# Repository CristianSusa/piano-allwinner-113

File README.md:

# Piano with Dev Board LCPI-PC-T113
This piano is a college project for Embedded Systems and Electronic Systems Design. It uses the LCPI-PC-T113 development board with the Allwinner T113s chip running embedded Debian. The project includes the design of the PCB as well as the design of the enclosure. Notes on the development process are also included.

## Contents
Within this repository, you will find two folders:
* embedded-systems-development
* electronic-system-design

These folders serve as a step-by-step guide on how to construct the piano. They include files, construction notes, and suggestions for improvements in future versions.

Enjoy :D

# The Project

This piano is designed to provide a low-cost solution for portable musical instruments.

It has two main functions:

1. **Piano Mode** – When a key is pressed, the corresponding note is played through the speaker, just as you would expect from a traditional piano.

2. **Tutor Mode** – In this mode, a few preset songs are available. You can select one, and LEDs will light up to indicate which key to press next, guiding you through the melody step by step.

The piano is intended not only to function as a musical instrument, but also to serve as a learning tool for beginners.

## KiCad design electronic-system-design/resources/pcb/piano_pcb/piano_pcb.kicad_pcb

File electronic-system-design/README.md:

# Electronic Design
This section provides a detailed explanation of the project's electronic design, including key decisions, objectives, and development rationale. It aims to offer a broader perspective on the piano as a finished product, beyond just its functionality.

## The Piano
This project is a university-level design that combines embedded systems and electronic hardware development. It is built around the LCPI-PC-T113 development board, featuring the Allwinner T113s chip running embedded Debian.

The piano integrates both custom PCB and enclosure design, with additional documentation on the development process.

Its goal is to offer a low-cost, portable musical instrument that serves both as a basic piano and as an educational tool. It features two main modes:

- **Piano Mode** – Pressing a key plays the corresponding note through a speaker.
- **Tutor Mode** – LEDs guide the user through preloaded melodies, indicating which key to press next.

The system is designed for beginners, blending play and learning in a compact, accessible format.

## Inspiration
This piano is physically inspired by commercial MIDI controllers such as the **MiniLab 3** by Arturia, the **Akai MPK Mini**, and the **OP-1** by Teenage Engineering.

The goal is to build a portable device that gives users easy access to a piano wherever they are.

## Objectives
The goal of this project is to create an affordable, efficient, and scalable digital keyboard that works as a standalone device. It features an intuitive user interface.

### Main Objective
Design and build an affordable, energy-efficient, and user-friendly digital keyboard with an intuitive interface, capable of functioning independently and suitable for educational or experimental use.

### Specific Objectives
- **Ensure accessibility and affordability** by keeping the total cost of components below $300,000 COP, making the device viable for students and academic institutions.
- **Promote usability and learning** by including exercises or songs, reinforcing its role as a musical tutor and learning tool.
- **Guarantee energy efficiency and portability** by ensuring the device operates with a current draw of less than 1.5 A, allowing it to be powered by a standard 5V / 2A USB adapter or computer.

## Block Diagram

The proposed system configuration uses the LCPI-PC-T113 development board, featuring the Allwinner T113-S3 chip, as the main controller. A custom daughterboard (the PCB designed in this course) interfaces with it to connect the piano peripherals.

This separation of boards allows modularity: the main board can be reused in future projects, while the daughterboard is application-specific.

The system consists of five main modules:

- **Piano Inputs** – Controls 25 keys (from C4 to C6, covering 2 octaves) arranged in a 5×5 matrix. A *74HC595* shift register activates the columns, while a *74HC165* shift register reads the row states.
  - Shift registers reduce the number of required GPIOs and allow scalable input/output control.
  - ✅ *Pro*: Efficient use of GPIOs with minimal pin usage.
  - ❌ *Con*: Adds a small delay due to serial communication and requires precise clocking.

- **User Interface** – Includes an OLED display and three menu buttons.
  - A minimal interface was chosen to ensure simplicity and ease of navigation for all users.
  - ✅ *Pro*: Clear feedback and interaction with minimal components.
  - ❌ *Con*: Limited interactivity and no text input options.

- **Piano Outputs** – Manages 25 LEDs (one per key) using two *74HC595* shift registers in a 5×5 matrix. Audio output is routed from the board’s headphone jack to an 8-ohm speaker.
  - Using a matrix configuration minimizes wiring and enables efficient LED control in tutor mode.
  - ✅ *Pro*: Clear visual guidance during learning.
  - ❌ *Con*: Cannot light multiple arbitrary combinations without flickering unless advanced multiplexing is implemented.

- **Power** – Powered via a USB-C port providing 5V @ 2A, allowing compatibility with standard smartphone chargers.
  - USB-C is a modern standard and widely available.
  - ✅ *Pro*: Universal and accessible power source.
  - ❌ *Con*: Some connectors have mechanical instability depending on the cable used.

- **Serial Communication and Data** – Includes SD card storage and USB to TTL serial communication used during development and booting.
  - External storage and serial communication simplify testing and firmware updates.
  - ✅ *Pro*: Easy debugging and access to external data.
  - ❌ *Con*: Required workaround (jumpers) due to missing TX/RX pins in the schematic.

## Electrical Schematic

A total of 19 pins are used to connect the processor to the piano's peripherals. The image below shows the pinout configuration:

This layout was chosen to optimize routing and prioritize low-latency signals, like the key matrix and OLED interface.

The following sections explain how each module works and how the components are connected. All images are taken from the project schematic file `piano_pcb.kicad_sch`, available at `./resources/pcb/piano_pcb`.

### Keys Matrix
A 5×5 matrix is used to detect key presses, allowing us to read 25 distinct notes. A *74HC595* shift register sequentially activates each column, and a *74HC165* reads the row values. The switches are configured with pull-down resistors: a pressed key outputs logic `1`, and an unpressed key outputs `0`.

- ✅ *Pro*: Scalable and compact solution for multiple key inputs.
- ❌ *Con*: Requires careful debouncing and timing control in software.

### LEDs Matrix
Another 5×5 matrix is used to control the LEDs, which are mainly used in tutor mode to highlight the next key to press. Two *74HC595* shift registers manage the LED activation. LEDs use a pull-down configuration: a LED lights up when its cathode is at logic `1` and its anode is at logic `0`.

Coupling capacitors were used in the four integrated circuits to ensure proper power connection.

- ✅ *Pro*: Clean and organized visual feedback system.
- ❌ *Con*: Without current control, simultaneous activation of many LEDs can overload the system.

### I2C Screen
Initially, a 240×240 SPI screen was proposed for the menu interface. However, due to technical issues and budget/time constraints, we opted for a 128×64 I2C OLED display using the SSD1306 controller.

- ✅ *Pro*: Easy to integrate, widely supported, and consumes less power.
- ❌ *Con*: Lower resolution limits UI complexity.

### Menu Buttons
Three buttons (`Left`, `Enter`, and `Right`) allow the user to navigate the interface. All buttons use a pull-down configuration: pressing a button results in logic `1`, and releasing it results in logic `0`.

- ✅ *Pro*: Simple and intuitive user interaction.
- ❌ *Con*: Limited to basic menu navigation without multi-directional input.

Once the device is powered on and the application starts, the main menu is displayed with two options:

1. **Piano Mode** – Basic mode in which pressing a key plays the corresponding sound.
2. **Tutor Mode** – Guides the user through one of four built-in songs: `Estrellita`, `Cumpleaños Feliz`, `Los Pollitos`, and `Piratas del Caribe`.

### Power Input
Power is supplied through a USB-C female connector, chosen for its compatibility with most modern chargers. However, this decision turned out to be suboptimal — in practice, the connection can be unstable depending on the cable or connector, causing accidental shutdowns with slight movement.

To protect the circuit, an SS14 diode prevents reverse current and voltage spikes. Two 5.1kΩ resistors to ground ensure the USB-C port is used strictly for power and limits voltage to 5V.

- ✅ *Pro*: Broad compatibility and compact form factor.
- ❌ *Con*: Susceptible to disconnection if cable or socket is loose.

### Dev Board Integration
A custom symbol and footprint were created in KiCad to represent the LCPI-PC-T113 board and ensure proper alignment of connections.

The schematic shows the necessary connections for:
- **Shift register control** – `SER`, `CLK`, `LATCH`
- **Menu buttons** – input GPIOs for `Left`, `Enter`, and `Right`
- **OLED display** – `SDA`, `SCL` for I2C communication

- ✅ *Pro*: Accurate mapping of dev board pins in PCB layout.
- ❌ *Con*: Omission of serial TX/RX was a critical error, requiring manual correction with jumpers.

The serial communication was originally assigned to pins `PE2` and `PE3`, as shown in the pinout image above. However, these connections were not included in the schematic — a design oversight. As a workaround, jumpers were added in the physical prototype. This is one of the areas identified for improvement in future revisions.

## Materials
The piano consists of low-cost electronic components, including standard switches, LEDs, and diodes. The two most expensive parts of the build are the LCPI-PC-T113 development board and the custom-designed daughterboard (PCB). These will be detailed further in the cost breakdown.

Below is a list of the main components used:

- 25 × Tactile switches (1 per key)
- 25 × Red LEDs (1 per key for tutor feedback)
- 25 × 220 Ω resistors (for LED current limiting)
- 50 × 1N4148 diodes (for matrix input protection)
- 8 × 10 kΩ resistors (for pull-down configurations)
- 3 × 4-leg tactile menu switches (Left, Enter, Right)
- 4 × 8×2 pin sockets (for shift register and board connections)
- 3 × 74HC595 shift registers (2 for LED matrix, 1 for key matrix column activation)
- 1 × 74HC165 shift register (for key matrix row reading)
- 4 × 100 nF ceramic capacitors (for decoupling)
- 1 × SS14 Schottky diode (for reverse polarity protection)
- 2 × 5.1 kΩ resistors (for USB-C power configuration)
- 1 × USB-C female port (for 5V power input)
- 2 × Female header grids (to interface with dev board)

All components were selected for availability, cost-efficiency, and compatibility with hand soldering and prototyping.

## PCB Design

KiCad and LayoutEditor were the main tools used to design the PCB. The complete KiCad project is available at `./resources/pcb/piano_pcb`.

Returning to our five main modules, this section covers the design process for each one.

---

### Piano Inputs

The key matrix relies on mechanical keyboard switches and diodes. [This video](https://www.youtube.com/watch?v=8WXpGTIbxlQ) provided valuable guidance on mechanical keyboard design and was used as a reference. Its symbol and footprint library was also integrated and is available in `./resources/pcb/piano_pcb/Resources`.

Each note has a dedicated LED, so the layout prioritizes compactness while replicating a traditional piano key arrangement. Diodes are placed to the left of each key to prevent ghosting, and LEDs are positioned above or below the switch based on the note's vertical position.

Footprint used for the key switches:

### Piano Outputs

The LEDs are a core feature for the tutor mode. Each LED has a dedicated 220 Ω current-limiting resistor and a 1N4148 diode to avoid unwanted activation due to matrix effects (ghosting).

### User Interface

The menu buttons and display are located on the top edge of the piano for visibility and accessibility. The OLED screen symbol and footprint were manually created based on an initial SPI version, though later adapted to a 128×64 I2C display (SSD1306). The chosen I2C pins remained the same for mechanical compatibility.

### Power Input

This section presented the most soldering challenges due to two surface-mount components: the USB-C female connector and the SS14 Schottky diode. These were the only compatible models available in the local market and required careful placement.

### Devboard Interface

A custom footprint was created to place female headers in a "shield-like" fashion, aligning with the LCPI-PC-T113 board’s pinout. This allows reliable and modular interfacing between the devboard and the daughterboard.

---

### Construction

The PCB routing was done using the `FreeRouting` tool. All traces were set to 0.5 mm width, which is sufficient given the low current requirements of each signal. Both top and bottom layers were used, with several vias placed throughout the board—particularly around the key and LED matrices—due to the high density of connections.

The PCB was manufactured by **JLCPCB**, and the production files are available at `./resources/pcb/piano_pcb/production`.

Below are some images of the PCB layout and the assembled board:

Final soldered board:

## Case Design

The case was designed using **Adobe Illustrator**, vectorizing the pieces for laser cutting. The main PCB measures **314 mm × 150.5 mm**, and additional clearance was considered for the height of the devboard underneath (~15 mm), as well as the switches and screen above (~17.5 mm).

The design consists of two main parts:

1. **The Case** – Made of MDF and laser cut to encase the piano. It protects the electronics and gives structural support.

2. **The Keycaps** – A piece of laser-cut acrylic simulates the shape of piano keys. The transparency allows LED light to shine through during tutor mode, guiding the user visually.

The Adobe Illustrator and PDF files used in the process are available at `./resources/case/files`.

### Case Construction

Once all pieces were laser cut, assembly was done manually. The result is a lightweight, solid enclosure with custom-fit keycaps:

## User Menu

As mentioned earlier, three buttons (`Left`, `Enter`, and `Right`) are used to navigate the user interface. All buttons follow a pull-down configuration: pressing a button sends logic `1`, and releasing it returns to logic `0`.

Upon powering on the device and loading the main application, the user is presented with the main menu featuring two options:

1. **Piano Mode** – A classic mode where each key press immediately plays a corresponding note.
2. **Tutor Mode** – A guided mode where the user can select one of four built-in songs: `Estrellita`, `Cumpleaños Feliz`, `Los Pollitos`, and `Piratas del Caribe`.

Below is a simplified flow diagram of the navigation logic:

Some photos of the interface in action:

## Prototype
The final piano is a mix of effort, enthusiasms, challenges, copper, mdf, acrilic, electrons and music. Here are some photos.

## Technical Decisions Justification

### Choice of Main Microcontroller or IC
The project uses the **LCPI-PC-T113** development board based on the **Allwinner T113-S3** processor. This chip was selected because it can run a full embedded Debian OS, providing enough processing power to handle multiple peripherals (display, inputs, outputs, audio) while offering flexibility for expansion. Its ability to support real-time applications (like those built with Faust) made it an ideal platform for this kind of project.

### Technology Type: THT, SMD, or Mixed
A **mixed technology approach** was used. Most components (resistors, diodes, capacitors, shift registers, buttons, LEDs) are **THT (Through-Hole Technology)**, selected for ease of manual soldering and local availability. However, some components such as the **USB-C connector** and the **SS14 diode** are **SMD (Surface-Mount Device)** because they were only available in that format.

This hybrid approach balanced manufacturability, cost, and the team's ability to assemble the board by hand.

### Number of Layers
The PCB was designed with **two layers (top and bottom)**. This was necessary to route the large number of signals—especially in the key and LED matrices—without increasing manufacturing costs. Vias were used to interconnect the layers where needed, allowing for a more compact and efficient layout.

### Power and EMI Considerations
Power is supplied through a **USB-C female connector**, delivering 5 V at 2 A. A **Schottky SS14 diode** was added to protect the circuit from reverse current or voltage spikes. Two **5.1 kΩ pull-down resistors** ensure the port is used for power only. The overall current draw of the system is low, so thermal or EMI (electromagnetic interference) concerns were minimal. However, filtering and shielding could be added in future revisions if needed.

### Standards Applied
While no formal certification standard was strictly followed, the design referenced general best practices from the **IPC-2221** standard, including trace width, clearance, and via placement. These practices helped ensure a manufacturable PCB and reliable electrical performance during testing.

---

## Possible Improvements

- **Redesign the pinout** to include the `TX` and `RX` serial communication lines. These were missing in the original schematic and had to be patched with jumpers on the prototype.
- **Replace or reposition the USB-C connector** to improve physical connection stability. In its current location, small movements can interrupt power and shut down the piano.
- **Use dedicated LED drivers**, such as the TLC5940, to enable PWM per channel, reduce sound delay, and allow multiple notes to play simultaneously (polyphony).
- **Reintroduce the SPI screen** if software support issues are resolved, to take advantage of its higher resolution for better UI design.
- **Optimize power consumption** by adding sleep modes or auto-shutdown after inactivity.
- **Add EMI protection and filtering** for use in more demanding environments or for future compliance with electronic certification.
- **Follow full IPC standards** (such as IPC-2222 for general-purpose PCBs) to improve reliability, documentation quality, and potential for scaling production.

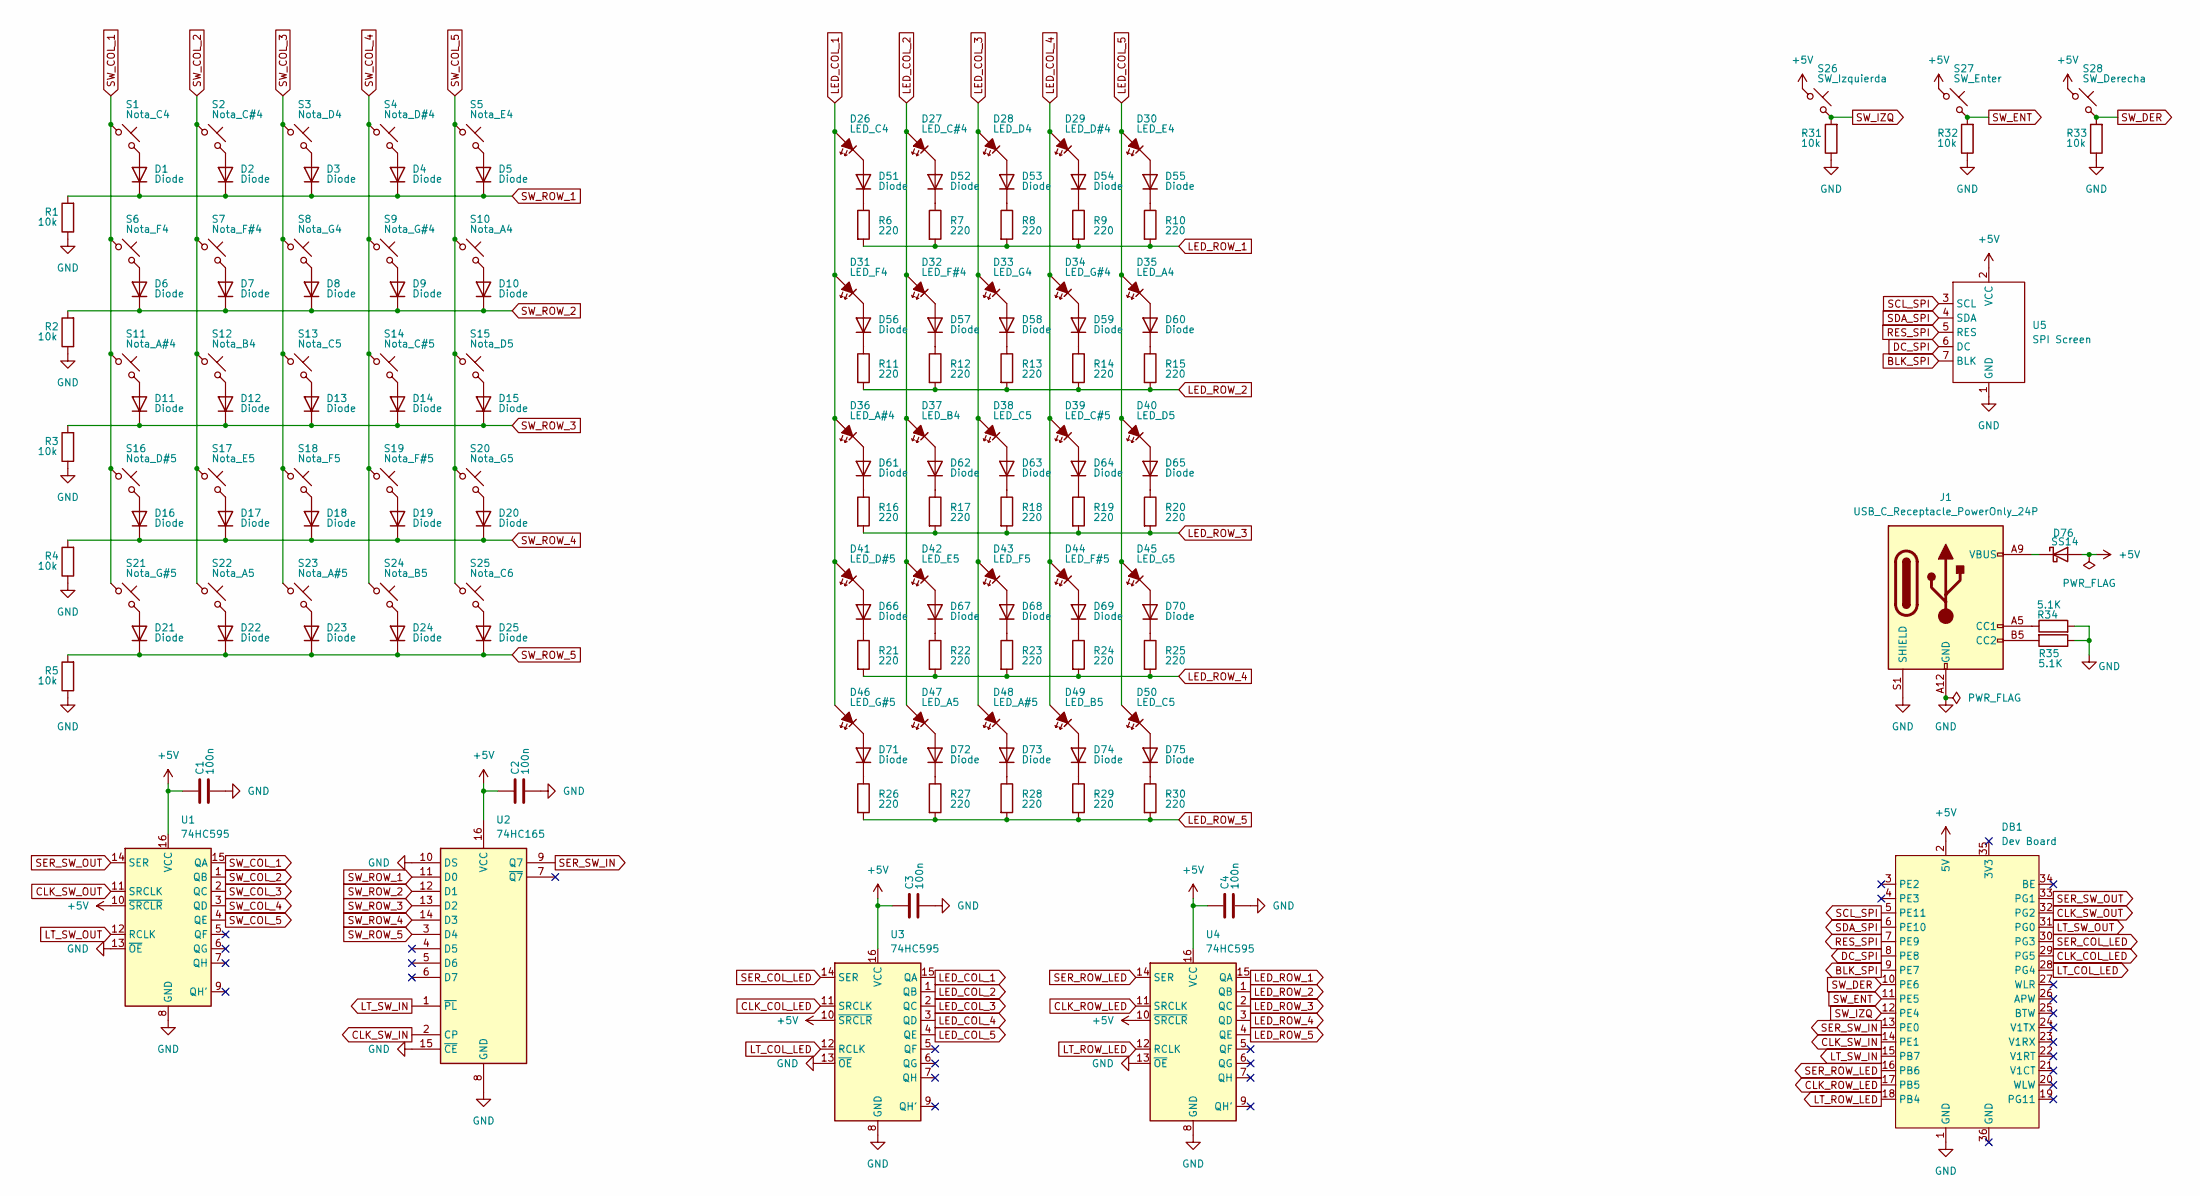
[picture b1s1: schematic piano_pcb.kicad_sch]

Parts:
C1, C2, C3, C4: 100n; CP_Radial_D8.0mm_P3.50mm
D1, D2, D3, D4, D5, D6, D7, D8, D9, D10, D11, D12, D13, D14, D15, D16, D17, D18, D19, D20, D21, D22, D23, D24, D25, D51, D52, D53, D54, D55, D56, D57, D58, D59, D60, D61, D62, D63, D64, D65, D66, D67, D68, D69, D70, D71, D72, D73, D74, D75: Diode; Diode_DO-35
D26: LED_C4; LED_D3.0mm
D27: LED_C#4; LED_D3.0mm
D28: LED_D4; LED_D3.0mm
D29: LED_D#4; LED_D3.0mm
D30: LED_E4; LED_D3.0mm
D31: LED_F4; LED_D3.0mm
D32: LED_F#4; LED_D3.0mm
D33: LED_G4; LED_D3.0mm
D34: LED_G#4; LED_D3.0mm
D35: LED_A4; LED_D3.0mm
D36: LED_A#4; LED_D3.0mm
D37: LED_B4; LED_D3.0mm
D38, D50: LED_C5; LED_D3.0mm
D39: LED_C#5; LED_D3.0mm
D40: LED_D5; LED_D3.0mm
D41: LED_D#5; LED_D3.0mm
D42: LED_E5; LED_D3.0mm
D43: LED_F5; LED_D3.0mm
D44: LED_F#5; LED_D3.0mm
D45: LED_G5; LED_D3.0mm
D46: LED_G#5; LED_D3.0mm
D47: LED_A5; LED_D3.0mm
D48: LED_A#5; LED_D3.0mm
D49: LED_B5; LED_D3.0mm
D76: SS14; D_SMA
DB1: Dev Board; Dev_Board_T113
J1: USB_C_Receptacle_PowerOnly_24P; USB_C_Receptacle_HRO_TYPE-C-31-M-17
R1, R2, R3, R4, R5, R31, R32, R33: 10k; R_Axial_DIN0204_L3.6mm_D1.6mm_P7.62mm_Horizontal
R6, R7, R8, R9, R10, R11, R12, R13, R14, R15, R16, R17, R18, R19, R20, R21, R22, R23, R24, R25, R26, R27, R28, R29, R30: 220; R_Axial_DIN0204_L3.6mm_D1.6mm_P7.62mm_Horizontal
R34, R35: 5.1K; R_Axial_DIN0204_L3.6mm_D1.6mm_P7.62mm_Horizontal
S1: Nota_C4; MX_PCB_1.00u
S2: Nota_C#4; MX_PCB_1.00u
S3: Nota_D4; MX_PCB_1.00u
S4: Nota_D#4; MX_PCB_1.00u
S5: Nota_E4; MX_PCB_1.00u
S6: Nota_F4; MX_PCB_1.00u
S7: Nota_F#4; MX_PCB_1.00u
S8: Nota_G4; MX_PCB_1.00u
S9: Nota_G#4; MX_PCB_1.00u
S10: Nota_A4; MX_PCB_1.00u
S11: Nota_A#4; MX_PCB_1.00u
S12: Nota_B4; MX_PCB_1.00u
S13: Nota_C5; MX_PCB_1.00u
S14: Nota_C#5; MX_PCB_1.00u
S15: Nota_D5; MX_PCB_1.00u
S16: Nota_D#5; MX_PCB_1.00u
S17: Nota_E5; MX_PCB_1.00u
S18: Nota_F5; MX_PCB_1.00u
S19: Nota_F#5; MX_PCB_1.00u
S20: Nota_G5; MX_PCB_1.00u
S21: Nota_G#5; MX_PCB_1.00u
S22: Nota_A5; MX_PCB_1.00u
S23: Nota_A#5; MX_PCB_1.00u
S24: Nota_B5; MX_PCB_1.00u
S25: Nota_C6; MX_PCB_1.00u
S26: SW_Izquierda; SW_PUSH_6mm_H5mm
S27: SW_Enter; SW_PUSH_6mm_H5mm
S28: SW_Derecha; SW_PUSH_6mm_H5mm
U1, U3, U4: 74HC595; DIP-16_W7.62mm_Socket_LongPads
U2: 74HC165; DIP-16_W7.62mm_Socket_LongPads
U5: SPI Screen; SPI_Screen

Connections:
+5V: C1.1, C2.1, C3.1, C4.1, D76.2 (A), DB1.2 (5V), S26.1, S27.1, S28.1, U1.10 (~SRCLR), U1.16 (VCC), U2.16 (VCC), U3.10 (~SRCLR), U3.16 (VCC), U4.10 (~SRCLR), U4.16 (VCC), U5.2 (VCC)
BLK_SPI: DB1.9 (PE7), U5.7 (BLK)
CLK_COL_LED: DB1.29 (PG5), U3.11 (SRCLK)
CLK_ROW_LED: DB1.17 (PB5), U4.11 (SRCLK)
CLK_SW_IN: DB1.14 (PE1), U2.2 (CP)
CLK_SW_OUT: DB1.32 (PG2), U1.11 (SRCLK)
DC_SPI: DB1.8 (PE8), U5.6 (DC)
GND: C1.2, C2.2, C3.2, C4.2, DB1.1 (GND), J1.A1 (GND), J1.A12 (GND), J1.B1 (GND), J1.B12 (GND), J1.S1 (SHIELD), R1.1, R2.1, R3.1, R4.1, R5.1, R31.1, R32.1, R33.1, R34.2, R35.1, U1.8 (GND), U1.13 (~OE), U2.8 (GND), U2.10 (DS), U2.15 (~CE), U3.8 (GND), U3.13 (~OE), U4.8 (GND), U4.13 (~OE), U5.1 (GND)
LED_COL_1: D26.2 (A), D31.2 (A), D36.2 (A), D41.2 (A), D46.2 (A), U3.15 (QA)
LED_COL_2: D27.2 (A), D32.2 (A), D37.2 (A), D42.2 (A), D47.2 (A), U3.1 (QB)
LED_COL_3: D28.2 (A), D33.2 (A), D38.2 (A), D43.2 (A), D48.2 (A), U3.2 (QC)
LED_COL_4: D29.2 (A), D34.2 (A), D39.2 (A), D44.2 (A), D49.2 (A), U3.3 (QD)
LED_COL_5: D30.2 (A), D35.2 (A), D40.2 (A), D45.2 (A), D50.2 (A), U3.4 (QE)
LED_ROW_1: R6.2, R7.2, R8.2, R9.2, R10.2, U4.15 (QA)
LED_ROW_2: R11.2, R12.2, R13.2, R14.2, R15.2, U4.1 (QB)
LED_ROW_3: R16.2, R17.2, R18.2, R19.2, R20.2, U4.2 (QC)
LED_ROW_4: R21.2, R22.2, R23.2, R24.2, R25.2, U4.3 (QD)
LED_ROW_5: R26.2, R27.2, R28.2, R29.2, R30.2, U4.4 (QE)
LT_COL_LED: DB1.28 (PG4), U3.12 (RCLK)
LT_ROW_LED: DB1.18 (PB4), U4.12 (RCLK)
LT_SW_IN: DB1.15 (PB7), U2.1 (~PL)
LT_SW_OUT: DB1.31 (PG0), U1.12 (RCLK)
unnamed: D1.2 (A), S1.2
unnamed: D2.2 (A), S2.2
unnamed: D3.2 (A), S3.2
unnamed: D4.2 (A), S4.2
unnamed: D5.2 (A), S5.2
unnamed: D6.2 (A), S6.2
unnamed: D7.2 (A), S7.2
unnamed: D8.2 (A), S8.2
unnamed: D9.2 (A), S9.2
unnamed: D10.2 (A), S10.2
unnamed: D11.2 (A), S11.2
unnamed: D12.2 (A), S12.2
unnamed: D13.2 (A), S13.2
unnamed: D14.2 (A), S14.2
unnamed: D15.2 (A), S15.2
unnamed: D16.2 (A), S16.2
unnamed: D17.2 (A), S17.2
unnamed: D18.2 (A), S18.2
unnamed: D19.2 (A), S19.2
unnamed: D20.2 (A), S20.2
unnamed: D21.2 (A), S21.2
unnamed: D22.2 (A), S22.2
unnamed: D23.2 (A), S23.2
unnamed: D24.2 (A), S24.2
unnamed: D25.2 (A), S25.2
unnamed: D26.1 (K), D51.2 (A)
unnamed: D27.1 (K), D52.2 (A)
unnamed: D28.1 (K), D53.2 (A)
unnamed: D29.1 (K), D54.2 (A)
unnamed: D30.1 (K), D55.2 (A)
unnamed: D31.1 (K), D56.2 (A)
unnamed: D32.1 (K), D57.2 (A)
unnamed: D33.1 (K), D58.2 (A)
unnamed: D34.1 (K), D59.2 (A)
unnamed: D35.1 (K), D60.2 (A)
unnamed: D36.1 (K), D61.2 (A)
unnamed: D37.1 (K), D62.2 (A)
unnamed: D38.1 (K), D63.2 (A)
unnamed: D39.1 (K), D64.2 (A)
unnamed: D40.1 (K), D65.2 (A)
unnamed: D41.1 (K), D66.2 (A)
unnamed: D42.1 (K), D67.2 (A)
unnamed: D43.1 (K), D68.2 (A)
unnamed: D44.1 (K), D69.2 (A)
unnamed: D45.1 (K), D70.2 (A)
unnamed: D46.1 (K), D71.2 (A)
unnamed: D47.1 (K), D72.2 (A)
unnamed: D48.1 (K), D73.2 (A)
unnamed: D49.1 (K), D74.2 (A)
unnamed: D50.1 (K), D75.2 (A)
unnamed: D51.1 (K), R6.1
unnamed: D52.1 (K), R7.1
unnamed: D53.1 (K), R8.1
unnamed: D54.1 (K), R9.1
unnamed: D55.1 (K), R10.1
unnamed: D56.1 (K), R11.1
unnamed: D57.1 (K), R12.1
unnamed: D58.1 (K), R13.1
unnamed: D59.1 (K), R14.1
unnamed: D60.1 (K), R15.1
unnamed: D61.1 (K), R16.1
unnamed: D62.1 (K), R17.1
unnamed: D63.1 (K), R18.1
unnamed: D64.1 (K), R19.1
unnamed: D65.1 (K), R20.1
unnamed: D66.1 (K), R21.1
unnamed: D67.1 (K), R22.1
unnamed: D68.1 (K), R23.1
unnamed: D69.1 (K), R24.1
unnamed: D70.1 (K), R25.1
unnamed: D71.1 (K), R26.1
unnamed: D72.1 (K), R27.1
unnamed: D73.1 (K), R28.1
unnamed: D74.1 (K), R29.1
unnamed: D75.1 (K), R30.1
unnamed: D76.1 (K), J1.A4 (VBUS), J1.A9 (VBUS), J1.B4 (VBUS), J1.B9 (VBUS)
unnamed: J1.A5 (CC1), R34.1
unnamed: J1.B5 (CC2), R35.2
RES_SPI: DB1.7 (PE9), U5.5 (RES)
SCL_SPI: DB1.5 (PE11), U5.3 (SCL)
SDA_SPI: DB1.6 (PE10), U5.4 (SDA)
SER_COL_LED: DB1.30 (PG3), U3.14 (SER)
SER_ROW_LED: DB1.16 (PB6), U4.14 (SER)
SER_SW_IN: DB1.13 (PE0), U2.9 (Q7)
SER_SW_OUT: DB1.33 (PG1), U1.14 (SER)
SW_COL_1: S1.1, S6.1, S11.1, S16.1, S21.1, U1.15 (QA)
SW_COL_2: S2.1, S7.1, S12.1, S17.1, S22.1, U1.1 (QB)
SW_COL_3: S3.1, S8.1, S13.1, S18.1, S23.1, U1.2 (QC)
SW_COL_4: S4.1, S9.1, S14.1, S19.1, S24.1, U1.3 (QD)
SW_COL_5: S5.1, S10.1, S15.1, S20.1, S25.1, U1.4 (QE)
SW_DER: DB1.10 (PE6), R33.2, S28.2
SW_ENT: DB1.11 (PE5), R32.2, S27.2
SW_IZQ: DB1.12 (PE4), R31.2, S26.2
SW_ROW_1: D1.1 (K), D2.1 (K), D3.1 (K), D4.1 (K), D5.1 (K), R1.2, U2.11 (D0)
SW_ROW_2: D6.1 (K), D7.1 (K), D8.1 (K), D9.1 (K), D10.1 (K), R2.2, U2.12 (D1)
SW_ROW_3: D11.1 (K), D12.1 (K), D13.1 (K), D14.1 (K), D15.1 (K), R3.2, U2.13 (D2)
SW_ROW_4: D16.1 (K), D17.1 (K), D18.1 (K), D19.1 (K), D20.1 (K), R4.2, U2.14 (D3)
SW_ROW_5: D21.1 (K), D22.1 (K), D23.1 (K), D24.1 (K), D25.1 (K), R5.2, U2.3 (D4)

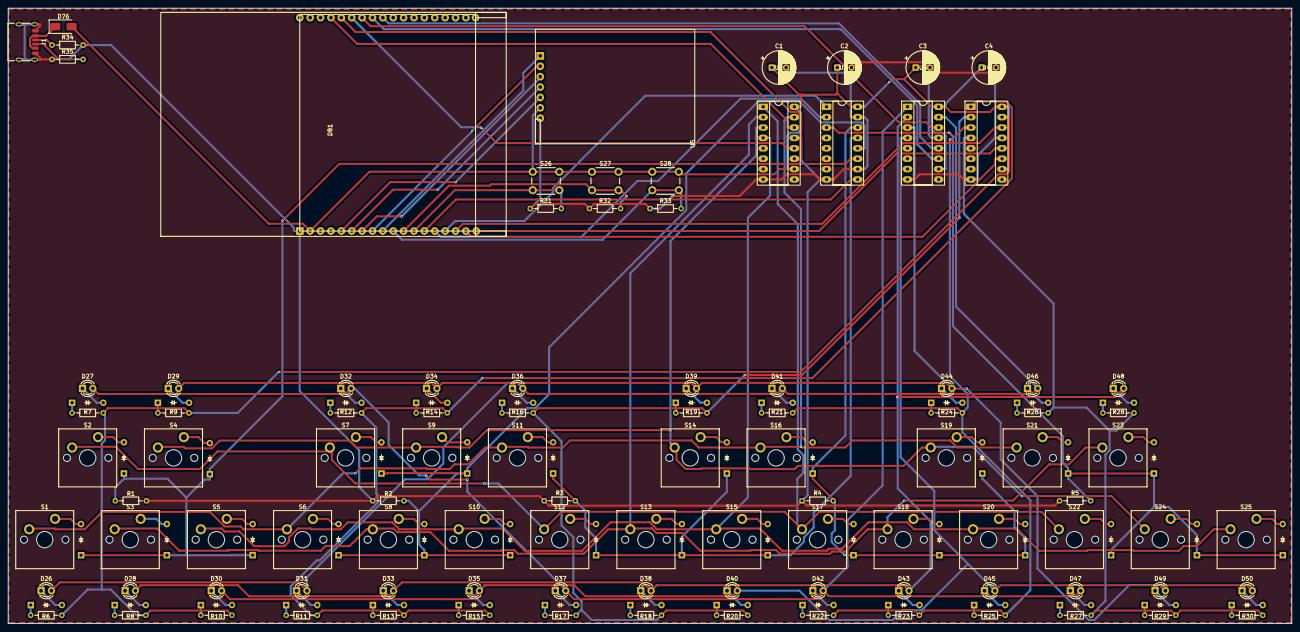
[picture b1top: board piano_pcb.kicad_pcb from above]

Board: 2 copper layers, 314.0 x 150.5 mm, 150 parts (0 on the bottom side), 120 nets.

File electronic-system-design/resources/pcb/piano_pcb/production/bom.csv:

Designator,Footprint,Quantity,Value,LCSC Part #
"C1, C2, C3, C4",CP_Radial_D8.0mm_P3.50mm,4,100n,
"D1, D10, D11, D12, D13, D14, D15, D16, D17, D18, D19, D2, D20, D21, D22, D23, D24, D25, D3, D4, D5, D51, D52, D53, D54, D55, D56, D57, D58, D59, D6, D60, D61, D62, D63, D64, D65, D66, D67, D68, D69, D7, D70, D71, D72, D73, D74, D75, D8, D9",Diode_DO-35,50,Diode,
D26,LED_D3.0mm,1,LED_C4,
D27,LED_D3.0mm,1,LED_C#4,
D28,LED_D3.0mm,1,LED_D4,
D29,LED_D3.0mm,1,LED_D#4,
D30,LED_D3.0mm,1,LED_E4,
D31,LED_D3.0mm,1,LED_F4,
D32,LED_D3.0mm,1,LED_F#4,
D33,LED_D3.0mm,1,LED_G4,
D34,LED_D3.0mm,1,LED_G#4,
D35,LED_D3.0mm,1,LED_A4,
D36,LED_D3.0mm,1,LED_A#4,
D37,LED_D3.0mm,1,LED_B4,
"D38, D50",LED_D3.0mm,2,LED_C5,
D39,LED_D3.0mm,1,LED_C#5,
D40,LED_D3.0mm,1,LED_D5,
D41,LED_D3.0mm,1,LED_D#5,
D42,LED_D3.0mm,1,LED_E5,
D43,LED_D3.0mm,1,LED_F5,
D44,LED_D3.0mm,1,LED_F#5,
D45,LED_D3.0mm,1,LED_G5,
D46,LED_D3.0mm,1,LED_G#5,
D47,LED_D3.0mm,1,LED_A5,
D48,LED_D3.0mm,1,LED_A#5,
D49,LED_D3.0mm,1,LED_B5,
D76,D_SMA,1,SS14,
DB1,Dev_Board_T113,1,Dev Board,
J1,USB_C_Receptacle_HRO_TYPE-C-31-M-17,1,USB_C_Receptacle_PowerOnly_24P,
"R1, R2, R3, R31, R32, R33, R4, R5",R_Axial_DIN0204_L3.6mm_D1.6mm_P7.62mm_Horizontal,8,10k,
"R10, R11, R12, R13, R14, R15, R16, R17, R18, R19, R20, R21, R22, R23, R24, R25, R26, R27, R28, R29, R30, R6, R7, R8, R9",R_Axial_DIN0204_L3.6mm_D1.6mm_P7.62mm_Horizontal,25,220,
"R34, R35",R_Axial_DIN0204_L3.6mm_D1.6mm_P7.62mm_Horizontal,2,5.1K,
S1,MX_PCB_1.00u,1,Nota_C4,
S10,MX_PCB_1.00u,1,Nota_A4,
S11,MX_PCB_1.00u,1,Nota_A#4,
S12,MX_PCB_1.00u,1,Nota_B4,
S13,MX_PCB_1.00u,1,Nota_C5,
S14,MX_PCB_1.00u,1,Nota_C#5,
S15,MX_PCB_1.00u,1,Nota_D5,
S16,MX_PCB_1.00u,1,Nota_D#5,
S17,MX_PCB_1.00u,1,Nota_E5,
S18,MX_PCB_1.00u,1,Nota_F5,
S19,MX_PCB_1.00u,1,Nota_F#5,
S2,MX_PCB_1.00u,1,Nota_C#4,
S20,MX_PCB_1.00u,1,Nota_G5,
S21,MX_PCB_1.00u,1,Nota_G#5,
S22,MX_PCB_1.00u,1,Nota_A5,
S23,MX_PCB_1.00u,1,Nota_A#5,
S24,MX_PCB_1.00u,1,Nota_B5,
S25,MX_PCB_1.00u,1,Nota_C6,
S26,SW_PUSH_6mm_H5mm,1,SW_Izquierda,
S27,SW_PUSH_6mm_H5mm,1,SW_Enter,
S28,SW_PUSH_6mm_H5mm,1,SW_Derecha,
S3,MX_PCB_1.00u,1,Nota_D4,
S4,MX_PCB_1.00u,1,Nota_D#4,
S5,MX_PCB_1.00u,1,Nota_E4,
S6,MX_PCB_1.00u,1,Nota_F4,
S7,MX_PCB_1.00u,1,Nota_F#4,
S8,MX_PCB_1.00u,1,Nota_G4,
S9,MX_PCB_1.00u,1,Nota_G#4,
"U1, U3, U4",DIP-16_W7.62mm_Socket_LongPads,3,74HC595,
U2,DIP-16_W7.62mm_Socket_LongPads,1,74HC165,
U5,SPI_Screen,1,SPI Screen,

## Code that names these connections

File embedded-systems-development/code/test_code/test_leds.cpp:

#include <gpiod.h>
#include <unistd.h>
#include <iostream>
#include <map>
#include <string>

#define CHIPNAME "gpiochip0"
#define CONSUMER "led-matrix-test"

// Pines columnas
#define PIN_SER_COL   195  // PG3
#define PIN_CLK_COL   197  // PG5
#define PIN_LATCH_COL 196  // PG4

// Pines filas
#define PIN_SER_ROW   38   // PB6
#define PIN_CLK_ROW   37   // PB5
#define PIN_LATCH_ROW 36   // PB4

// Notas organizadas por [columna][fila]
const char* notes[5][5] = {
    {"C4",  "F4",  "A#4", "D#5", "G#5"},
    {"C#4", "F#4", "B4",  "E5",  "A5"},
    {"D4",  "G4",  "C5",  "F5",  "A#5"},
    {"D#4", "G#4", "C#5", "F#5", "B5"},
    {"E4",  "A4",  "D5",  "G5",  "C6"}
};

gpiod_chip *chip;
gpiod_line *serCol, *clkCol, *latchCol;
gpiod_line *serRow, *clkRow, *latchRow;

void pulse(gpiod_line* line) {
    gpiod_line_set_value(line, 1);
    usleep(1);
    gpiod_line_set_value(line, 0);
    usleep(1);
}

bool setup() {
    chip = gpiod_chip_open_by_name(CHIPNAME);
    if (!chip) return false;

    serCol   = gpiod_chip_get_line(chip, PIN_SER_COL);
    clkCol   = gpiod_chip_get_line(chip, PIN_CLK_COL);
    latchCol = gpiod_chip_get_line(chip, PIN_LATCH_COL);

    serRow   = gpiod_chip_get_line(chip, PIN_SER_ROW);
    clkRow   = gpiod_chip_get_line(chip, PIN_CLK_ROW);
    latchRow = gpiod_chip_get_line(chip, PIN_LATCH_ROW);

    if (!serCol || !clkCol || !latchCol || !serRow || !clkRow || !latchRow)
        return false;

    if (gpiod_line_request_output(serCol, CONSUMER, 0) < 0 ||
        gpiod_line_request_output(clkCol, CONSUMER, 0) < 0 ||
        gpiod_line_request_output(latchCol, CONSUMER, 0) < 0 ||
        gpiod_line_request_output(serRow, CONSUMER, 0) < 0 ||
        gpiod_line_request_output(clkRow, CONSUMER, 0) < 0 ||
        gpiod_line_request_output(latchRow, CONSUMER, 0) < 0)
        return false;

    return true;
}

void shiftOut(gpiod_line* data, gpiod_line* clk, gpiod_line* latch, uint8_t val) {
    for (int i = 7; i >= 0; --i) {
        int bit = (val >> i) & 1;
        gpiod_line_set_value(data, bit);
        pulse(clk);
    }
    pulse(latch);
}

// Encender una nota específica
void lightNote(std::string note, const std::map<std::string, std::pair<int, int>>& noteToPosition) {
    auto it = noteToPosition.find(note);
    if (it == noteToPosition.end()) {
        std::cerr << "Nota no encontrada: " << note << std::endl;
        return;
    }

    int col = it->second.first;
    int row = it->second.second;

    uint8_t colMask = 1 << col;
    uint8_t rowMask = ~(1 << row);  // lógica inversa

    shiftOut(serCol, clkCol, latchCol, colMask);
    shiftOut(serRow, clkRow, latchRow, rowMask);
}

int main() {
    if (!setup()) {
        std::cerr << "Error al inicializar GPIOs\n";
        return 1;
    }

    std::map<std::string, std::pair<int, int>> noteToPosition;

    // Generar el mapeo inverso
    for (int col = 0; col < 5; ++col) {
        for (int row = 0; row < 5; ++row) {
            noteToPosition[notes[col][row]] = {col, row};
        }
    }

    // Barrido de todas las notas del piano
    const char* testNotes[] = {
        "C4", "C#4", "D4", "D#4", "E4", "F4", "F#4", "G4", "G#4",
        "A4", "A#4", "B4", "C5", "C#5", "D5", "D#5", "E5", "F5",
        "F#5", "G5", "G#5", "A5", "A#5", "B5", "C6"
    };

    for (const auto& note : testNotes) {
        std::cout << "Encendiendo nota: " << note << std::endl;
        lightNote(note, noteToPosition);
        usleep(300000);  // 300 ms
    }

    // Apagar todo
    shiftOut(serCol, clkCol, latchCol, 0);
    shiftOut(serRow, clkRow, latchRow, 0);
    gpiod_chip_close(chip);

    return 0;
}

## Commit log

2025-07-24 Update README.md and files
2025-07-24 Update README.md and images
2025-07-25 Update electronic-system-design folder
2025-07-25 Update PCB files
2025-07-25 Update case files
2025-07-25 Update Prototype and Improvements section
